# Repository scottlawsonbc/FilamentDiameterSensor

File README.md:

# FilamentDiameterSensor

ENPH 459 - Engineering Physics Project I
----------------------------------------
A Non-contact Diameter Measurement Device for 3D Printers and Filament Manufacturing

The filament diameter sensor is based on the STM32F4 and uses a two-axis optical sensor to get an accurate measurement of filament diameter without contacting the filament.
This makes the sensor especially suited for filament production since it can measure filament diameter even when it is soft and not able to be measured with physical methods.

The sensor uses two laser diodes as coherent light sources and two photodiode arrays (like a single row camera) which rapidly measure the diameter.

The project includes a simulator which models the optical system and allows different measurement functions to be tested with it.

When used with a special build of Marlin firmware, print quality improves significantly.

### File Organization ###

1.  *Arduino* - 
    Initial prototype was implemented for Arduino.

2.  *Code* - 
    Includes the rest of the project's (non-MATLAB) code. Several versions of the shadow-simulator, a fork of the printer firmware Marlin(modified to interface with the filament sensor), and the sensor's firmware to be run on a STM32F3 development board.
    
3.  *Eagle* - 
    PCB layout files for the photodiode array (TSL1402CL) breakout board.
    
4.  *Matlab* - 
    Matlab script used to measure the relative print quality based on the roughness of vertical printed edges.

5.  *Pictures* - 
    Pictures from the sensor development and print quality testing.

6.  *Reference Documents* - 
    Documentation for the STM32F3 development board, the linear photodiode array used in the sensor, and the prototype sensor.
    
7.  *Solidworks* - 
    All 3D design for the sensor, mostly Solidworks with some .STL-rasterized models for 3D printing.

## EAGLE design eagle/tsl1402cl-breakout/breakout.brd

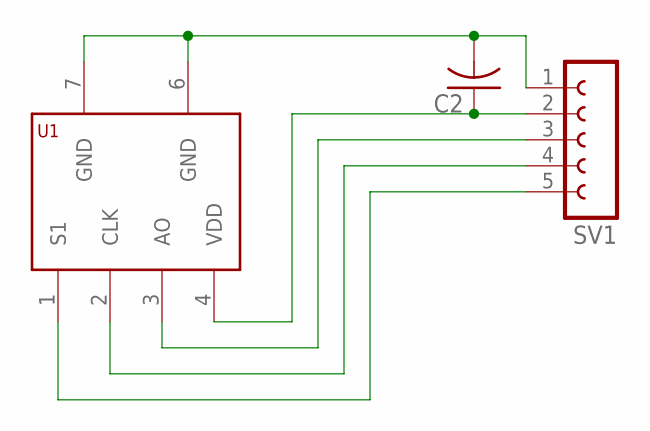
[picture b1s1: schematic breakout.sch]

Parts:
C2: C-US025-030X050; C025-030X050
SV1: FE05-1
U1: TSL1401CL; TSL8

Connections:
unnamed: C2.2, SV1.1, U1.6 (GND), U1.7 (GND)
unnamed: C2.1, SV1.2, U1.4 (VDD)
unnamed: SV1.3, U1.3 (AO)
unnamed: SV1.4, U1.2 (CLK)
unnamed: SV1.5, U1.1 (S1)

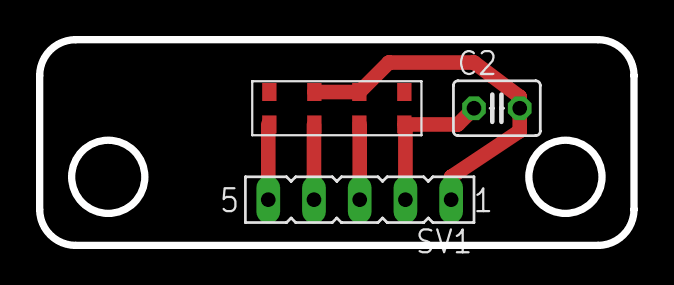
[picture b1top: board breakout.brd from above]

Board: 2 copper layers, 33.0 x 11.4 mm, 3 parts (0 on the bottom side), 5 nets.

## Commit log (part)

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2014-12-26 :octocat: Added .gitattributes & .gitignore files
2014-12-26 Initial code commit
    Added edge detector code
2014-12-26 Optimized finite differences function by removing the division (Rowan's suggestion). Made 53% improvement in speed for this function
2015-01-05 Added module to compute a moving average of measurements
2015-01-05 Changed output of edge_detector.pde
    Edge_detector.pde now uses the moving average modle
2015-01-05 Moved arduino code into separate folder
2015-01-07 Added line to .gitignore for Solidworks temp files
2015-01-08 Removed the out of date test project files
2015-01-09 Revert "Added new stm32f3 solution files"
    This reverts commit 59841e8545f10ac5b27632c7f518e71ee6c6ccc7.
2015-01-09 Updated ignore file
2015-01-09 Update gitignore to ignore *.opensdf files
2015-01-09 Updated gitignore
2015-01-10 Created an updated breakout PCB for the TSL1401CL sensor
    Used EAGLE CAD to design a breakout board PCB for the TSL1401CL sensor.
    Eight of the breakout boards are being fabricated on the LPKF protomat
    PCB mill.
    The breakout boards will be used to develop several 2-axis filament
    sensor prototypes over the next few weeks.
    The breakout board pinout can be found in the datasheet for the
2015-01-12 Added lots of documentation and datasheets, soldered PCBs
    Designed TSL1401Cl breakout boards in EAGLE and milled eight of them in
    the project lab PCB mill. Soldered five of the boards and four of them
    are working, one appears to have a short circuit possibly caused by
    inaccessible solder paste or excessive heat when soldering.
    I wrote the pinout on the breakout boards, but the pins can also be
    found in the TSL1401CL datasheet.
2015-01-15 Changed one comment in the TSL module
    Updated the function comment for the TSL module to be more clear.
    Explains how the function starts an output cycle for the TSL1401CL
    sensor. For a full description of how the TSL1401CL sensor works,
    consult the datasheet in the reference documentation folder.
2015-01-15 Created a two-axis filament diameter sensor simulator in C#
    Developed a graphical simulator in C# to visualize the two-axis edge
    detection sensor.
    [Instructions]
    The LEDs, sensors, and filament can be moved by dragging and dropping
    the shapes. To constrain movement to be vertical, hold the 'Z' key when
    dragging. To constrain movement to be horizontal, hold the 'X' key.
2015-01-17 Fixed class in default DiameterCalculator user code
    changed from class X to class DiameterCalculator
2015-01-17 Reverted revert for code update
2015-01-19 Made a simulator in Solidworks
2015-01-26 Initial commit of 2-axis prototype sensor CAD files
    Assembly
    - Chassis
    - Lid
2015-02-08 Updated default code for the real-time code execution
    Changed the default code that is generated for the real time code
    execution. This update fixes errors in the coordinate system.
    Previously, the coordinates were being scaled by 2.0 instead of 20.0,
    and one of the values was negative instead of positive.
2015-02-09 Added Matlab code used to generate some 2-axis math
    Finds the symbolic representation of the intersection of the two
    filament-center-lines. This point gives the coordinates (fil_x, fil_y)
    of the filament's center.
2015-02-12 Revert "Initial commit of 2-axis diameter geometry math"
    This reverts commit dee4b4a718e5d217a961d3bdd8144f5a0bca2bbd.
2015-02-12 Updated 2-axis math to take floats as input
    2-axis math (geometry.c) now takes in float variables (the positions of
    the shadows along the TSL1401 sensor). The offsets of the TSL's from the
    filament sensor's origin were added as constants to geometry.h .
    This allows the 2-axis math to be used with the current sub-pixel
    function.
2015-02-14 Added support for dual ADC measurements
    The STM32F3 contains two fast ADCs, ADC1 and ADC2, which are tightly
    coupled and can be utilized in a master-slave configuration. Both ADCs
    can be triggered to start a conversion simultaneously and the conversion
    value can be read in parallel.
    I've changed the initialization functions for the ADC peripherals so
    that they operate in Regular Simultaneous Mode, which will allow us to
2015-02-14 Revert "Minor refactor of GEO module"
    This reverts commit c43f08f81f811c04336f6d19f8d5d6ee2f59607c.
2015-02-14 Moved geometry.h and geometry.c to the correct source code folder
    Sorry, Rowan. I hope you don't have uncommitted changes that will cause
    a merge conflict. I relocated the geometry files to the correct source
    code folder. Right now geometry.h cannot easily be imported by other
    source code files.
2015-02-14 Changed <math.h> function calls in geometry.c
    Replaced calls to the math.h functions with the proper floating point
    version of the function. FPU instructions are not compatible with double
    precision floats.
2015-02-14 Updated pin definitions for 2-axis prototype
    Changed some of the pin definitions in preparation for the two axis
    prototype
2015-02-14 New optimization settings and makefile
2015-02-14 Added three pictures of the two axis sensor pinout
    Uploaded three pictures of how the two axis sensor can connect to the
    STM32F3 discovery board.
2015-02-15 Changed some coordinates around in the geometry file
    Currently being debugged. Something is wrong
2015-02-15 Added a width parameter to the TSL module
2015-02-22 Comment typo correction in geometry.h /.c
2015-02-26 Improved fit for 2-axis prototype's lid & insert
    Updated Solidworks models for 2-axis prototype: improved fit (via
    margins) and added a lid insert variation (see feature tree in "Lid
    Insert.SLDPRT") for holding a piece of 3mm filament steady, in the
    approximate center of the sensing area.
2015-02-28 Geometry bug-fix and changes to two constants
    Corrected the inputs to geometry math: E1 and E0 for the B sensor were
    mixed up.
    Changed the number of iterations for sensor data averaging to 300.
    Changed the integration time for each reading to 0.
    Fixed the end condition for iteration counting.
    Deleted old geometry math code.
2015-02-28 Removed debug print function name overlap
    dprintf( ) is now uprintf( ) to remove overlap with the c-library
    function dprintf( )
2015-03-09 Added 'large' configuration to 2-axis prototype.
    LED-sensor distance changed to 130mm.
    LED mounting changed to fit small high-brightness LEDs.
    Note: I noticed that some of the LED-sensor distances are not defined
    accurately for the previous 2-axis sensor prototype. I will be
    correcting these: should improve math accuracy.
2015-03-16 Added a new I2C communication module
    Added a new module for I2C communication to the sensor code. The only
    dependency for this code is the STMicroelectronics STM32F3 standard
    peripheral library. The current code also includes a rudimentary
    bit-bang implementation of I2C communication for debugging purposes
    (commented out).
    The I2C module in the standard peripheral library is complex and
2015-03-19 Fixed github commitment issues
2015-03-20 Comment corrections in edge-detection
2015-03-21 Updated pin definitions for TSL1401CL
    Changed the ADC, serial, and clock pins for the TSL1401CL sensor. The
    pin changes were made to relocate sensor pins to be closer to the sensor
    to reduce wiring clutter. No functional changes made.
2015-03-21 Added updated GEO constants for small 2-axis sensor
2015-03-21 Added 130mm printer-adapted sensor geometry values
    Organized the various geometry constants based on the sensor type in
    use: can define a preset sensor geometry in geometry.h or use a custom
    geometry.
2015-03-21 wtf github
2015-03-22 Added printer-adapted sensor prototype models
    Made 2 changes since printing and assembling the models:
    - Made the mounting protrusion on the printer-adapted-chassis longer (6
    -> 12mm) so that the next iteration will not need nylon standoffs to
    line up with the cold end.
    - Moved the clearance slots on the printer-adapted-board mount for the
    board's underside pins so that the board fits properly.
2015-03-22 Additional averaging in main.c
    Changed the number of iterations from 300 to 6000 which substantially
    increases the amount of sensor averaging. After making this change, the
    output of the sensor is much more stable, and changes every couple of
    seconds. Commented out I2C and USART references to increase execution
    speed.
2015-03-23 Improved I2C slave code
    Improved code for acting as a slave in I2C communication. Uses polling
    functions found in the STM32 standard peripheral library instead of
    interrupt based functions. Tested communication with a Bus Pirate to
    verify correct I2C communication
2015-03-23 Added a circular buffer module (RING)
    Added a new module with a circular buffer that could potentially be used
    to let the sensor handle the filament buffer instead of the printer
    firmware (to reduce ram usage). The STM32 has significantly more excess
    ram than the Atmega processor. This code should work, but is not
    currently used by any other module.
2015-03-24 Fixed bugs in both Box Filter functions
    In (old) BoxFilter: there used to be a bug where the averaged value for
    x[i] was subtracted from the moving sum instead of the old value for
    x[i].
    In (new) CenteredBoxFilter: the (M+1)th last value was never changed,
    where M is the box filter length. This lead to a large difference being
    picked up by the difference function, making an edge get detected nearly
2015-03-25 Changed sensor default state to OFF
2015-03-25 Added Arduino program for testing I2C communication
    Added slave_test.ino to code folder. This test code sends I2Ccommands
    from an arduino device using the Wire library to the STM32 sensor and
    prints the output to serial.
2015-03-25 added enph 459 tags to firmware
2015-03-26 Fixed a header file import error
    Accidentally imported "i2c_filament_sensor.cpp" instead of
    "i2c_filament_sensor.h". This is now fixed.
2015-03-27 Fixed bug in I2C code. Added interrupt support for I2C.
    Added interrupt based support for I2C code. This allows the device to
    respond much more quickly than with the previous polling based
    approached.
2015-03-29 Added new printing function separate from existing uprintf
    New function that will not get disabled when uprintf is disabled. This
    is used for non-debugging serial output
2015-03-29 Added new volumetric multiplier to main.c
2015-03-29 Added volumetric ratio buffer functions to sensor
2015-03-29 bug fixes in i2c support
2015-03-30 Added IIR output filter to sensor
    The sensor will now filter the output (in addition to filtering the
    input pixel values). This IIR filter will prevent rapid step changes in
    filament diameter measurements. New measurements are now computed as:
    x_(i+1) = ((15*x_i) + (new measurement)) / 16, and the constants 15, 1,
    16 can be modified as define macros.
2016-03-16 Added README.md
2017-03-25 Add images of sensor, simulator, and results
